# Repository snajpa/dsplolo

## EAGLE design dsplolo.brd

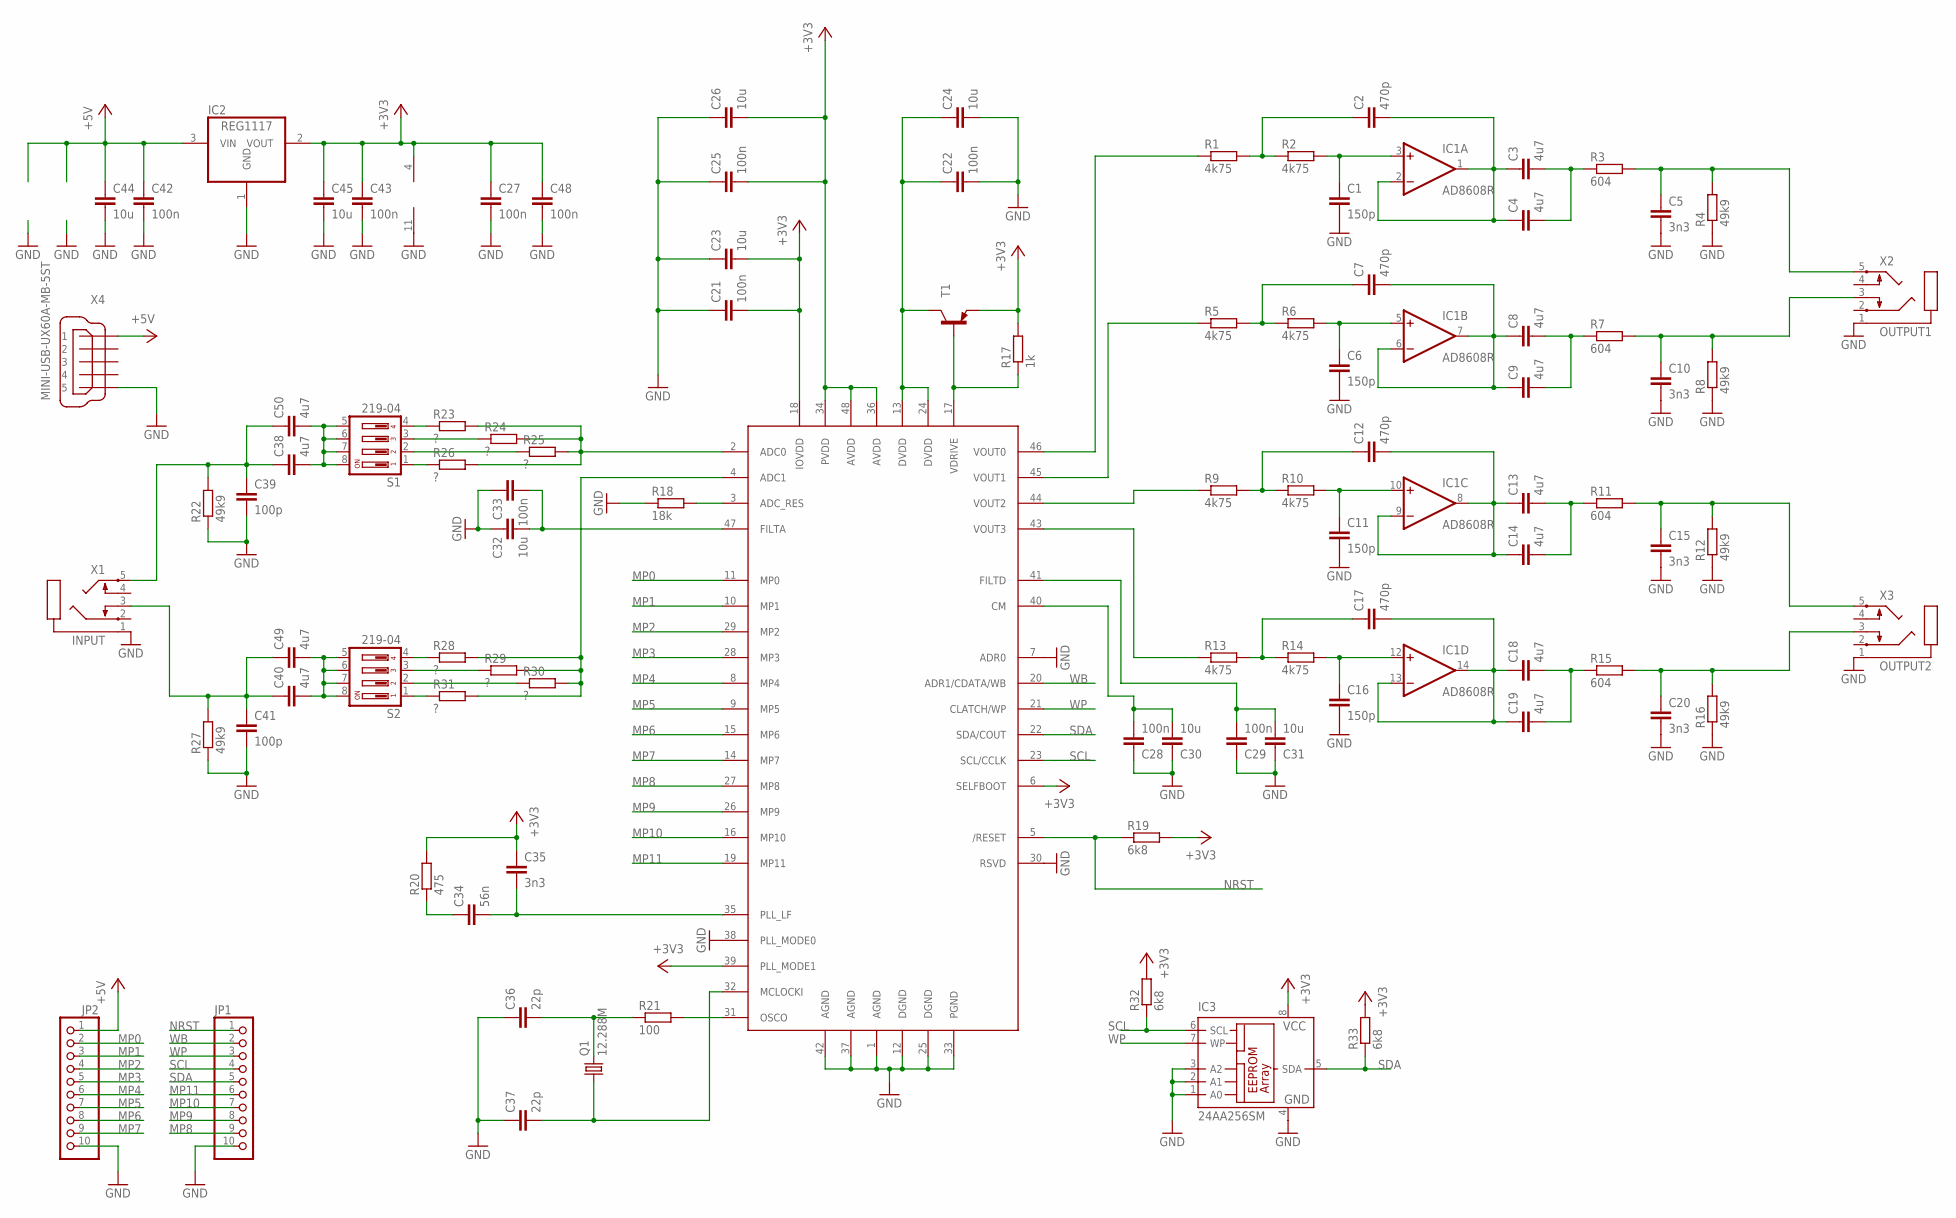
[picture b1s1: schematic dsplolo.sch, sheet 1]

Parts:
C1, C6, C11, C16: 150p; C1206
C2, C7, C12, C17: 470p; C1206
C3, C4, C8, C9, C13, C14, C18, C19, C38, C40, C49, C50: 4u7; C1206
C5, C10, C15, C20, C35: 3n3; C1206
C21, C22, C25, C27, C28, C29, C33, C42, C43, C48: 100n; C1206
C23, C24, C26, C30, C31, C32, C44, C45: 10u; C1206
C34: 56n; C1206
C36, C37: 22p; C1206
C39, C41: 100p; C1206
IC1: AD8608R; SO-14
IC2: REG1117; SOT223
IC3: 24AA256SM; SO-08M
JP1, JP2: PINHD-1X10; 1X10
Q1: 12.288M; HC49UP
R1, R2, R5, R6, R9, R10, R13, R14: 4k75; R1206
R3, R7, R11, R15: 604; R1206
R4, R8, R12, R16, R22, R27: 49k9; R1206
R17: 1k; R1206
R18: 18k; R1206
R19, R32, R33: 6k8; R1206
R20: 475; R1206
R21: 100; R1206
R23, R24, R25, R26, R28, R29, R30, R31: ?; R1206
S1, S2: 219-04; CTS-219-04
T1: BC857C-PNP-SOT23-BEC; SOT23-BEC
U$1: ADAU1701; LQFP-48
X1: INPUT; STX3100
X2: OUTPUT1; STX3100
X3: OUTPUT2; STX3100
X4: MINI-USB-UX60A-MB-5ST; UX60A-MB-5ST

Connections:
+3V3: C21.2, C23.2, C25.2, C26.2, C27.1, C35.1, C43.1, C45.1, C48.1, IC1.4 (V+), IC2.2 (VOUT), IC3.8 (VCC), R17.2, R19.2, R20.2, R32.2, R33.2, T1.E, U$1.6 (SELFBOOT), U$1.18 (IOVDD), U$1.34 (PVDD), U$1.36 (AVDD), U$1.39 (PLL_MODE1), U$1.48 (AVDD)
+5V: C42.1, C44.1, IC2.3 (VIN), JP2.1, X4.1
GND: C1.2, C5.2, C6.2, C10.2, C11.2, C15.2, C16.2, C20.2, C21.1, C22.2, C23.1, C24.2, C25.1, C26.1, C27.2, C28.1, C29.1, C30.1, C31.1, C32.1, C33.1, C36.1, C37.1, C39.2, C41.2, C42.2, C43.2, C44.2, C45.2, C48.2, IC1.11 (V-), IC2.1 (GND), IC3.1 (A0), IC3.2 (A1), IC3.3 (A2), IC3.4 (GND), JP1.10, JP2.10, R4.1, R8.1, R12.1, R16.1, R18.1, R22.1, R27.1, U$1.1 (AGND), U$1.7 (ADR0), U$1.12 (DGND), U$1.25 (DGND), U$1.30 (RSVD), U$1.33 (PGND), U$1.37 (AGND), U$1.38 (PLL_MODE0), U$1.42 (AGND), X1.1, X2.1, X3.1, X4.5
MP0: JP2.2, U$1.11 (MP0)
MP1: JP2.3, U$1.10 (MP1)
MP2: JP2.4, U$1.29 (MP2)
MP3: JP2.5, U$1.28 (MP3)
MP4: JP2.6, U$1.8 (MP4)
MP5: JP2.7, U$1.9 (MP5)
MP6: JP2.8, U$1.15 (MP6)
MP7: JP2.9, U$1.14 (MP7)
MP8: JP1.9, U$1.27 (MP8)
MP9: JP1.8, U$1.26 (MP9)
MP10: JP1.7, U$1.16 (MP10)
MP11: JP1.6, U$1.19 (MP11)
unnamed: C8.2, C9.2, R7.1
unnamed: C3.2, C4.2, R3.1
unnamed: C5.1, R3.2, R4.2, X2.5
unnamed: C2.1, R1.2, R2.1
unnamed: C1.1, IC1.3 (+IN), R2.2
unnamed: C2.2, C3.1, C4.1, IC1.1 (OUT), IC1.2 (-IN)
unnamed: C10.1, R7.2, R8.2, X2.3
unnamed: C7.1, R5.2, R6.1
unnamed: C6.1, IC1.5 (+IN), R6.2
unnamed: C7.2, C8.1, C9.1, IC1.6 (-IN), IC1.7 (OUT)
unnamed: C13.2, C14.2, R11.1
unnamed: C15.1, R11.2, R12.2, X3.5
unnamed: C12.1, R9.2, R10.1
unnamed: C11.1, IC1.10 (+IN), R10.2
unnamed: C12.2, C13.1, C14.1, IC1.8 (OUT), IC1.9 (-IN)
unnamed: C18.2, C19.2, R15.1
unnamed: C20.1, R15.2, R16.2, X3.3
unnamed: C17.1, R13.2, R14.1
unnamed: C16.1, IC1.12 (+IN), R14.2
unnamed: C17.2, C18.1, C19.1, IC1.13 (-IN), IC1.14 (OUT)
unnamed: R18.2, U$1.3 (ADC_RES)
unnamed: C22.1, C24.1, T1.C, U$1.13 (DVDD), U$1.24 (DVDD)
unnamed: R17.1, T1.B, U$1.17 (VDRIVE)
unnamed: R1.1, U$1.46 (VOUT0)
unnamed: R5.1, U$1.45 (VOUT1)
unnamed: R9.1, U$1.44 (VOUT2)
unnamed: R13.1, U$1.43 (VOUT3)
unnamed: C32.2, C33.2, U$1.47 (FILTA)
unnamed: C37.2, Q1.1, U$1.32 (MCLOCKI)
unnamed: C29.2, C31.2, U$1.41 (FILTD)
unnamed: C28.2, C30.2, U$1.40 (CM)
unnamed: C34.2, C35.2, U$1.35 (PLL_LF)
unnamed: C34.1, R20.1
unnamed: C36.2, Q1.2, R21.1
unnamed: R21.2, U$1.31 (OSCO)
unnamed: R23.1, S1.4
unnamed: C38.1, C39.1, C50.1, R22.2, X1.5
unnamed: C38.2, C50.2, S1.5, S1.6, S1.7, S1.8
unnamed: R24.1, S1.3
unnamed: R25.1, S1.2
unnamed: R26.1, S1.1
unnamed: R23.2, R24.2, R25.2, R26.2, U$1.2 (ADC0)
unnamed: C40.1, C41.1, C49.1, R27.2, X1.3
unnamed: C40.2, C49.2, S2.5, S2.6, S2.7, S2.8
unnamed: R28.1, S2.4
unnamed: R29.1, S2.3
unnamed: R30.1, S2.2
unnamed: R31.1, S2.1
unnamed: R28.2, R29.2, R30.2, R31.2, U$1.4 (ADC1)
NRST: JP1.1, R19.1, U$1.5 (/RESET)
SCL: IC3.6 (SCL), JP1.4, R32.1, U$1.23 (SCL/CCLK)
SDA: IC3.5 (SDA), JP1.5, R33.1, U$1.22 (SDA/COUT)
WB: JP1.2, U$1.20 (ADR1/CDATA/WB)
WP: IC3.7 (WP), JP1.3, U$1.21 (CLATCH/WP)

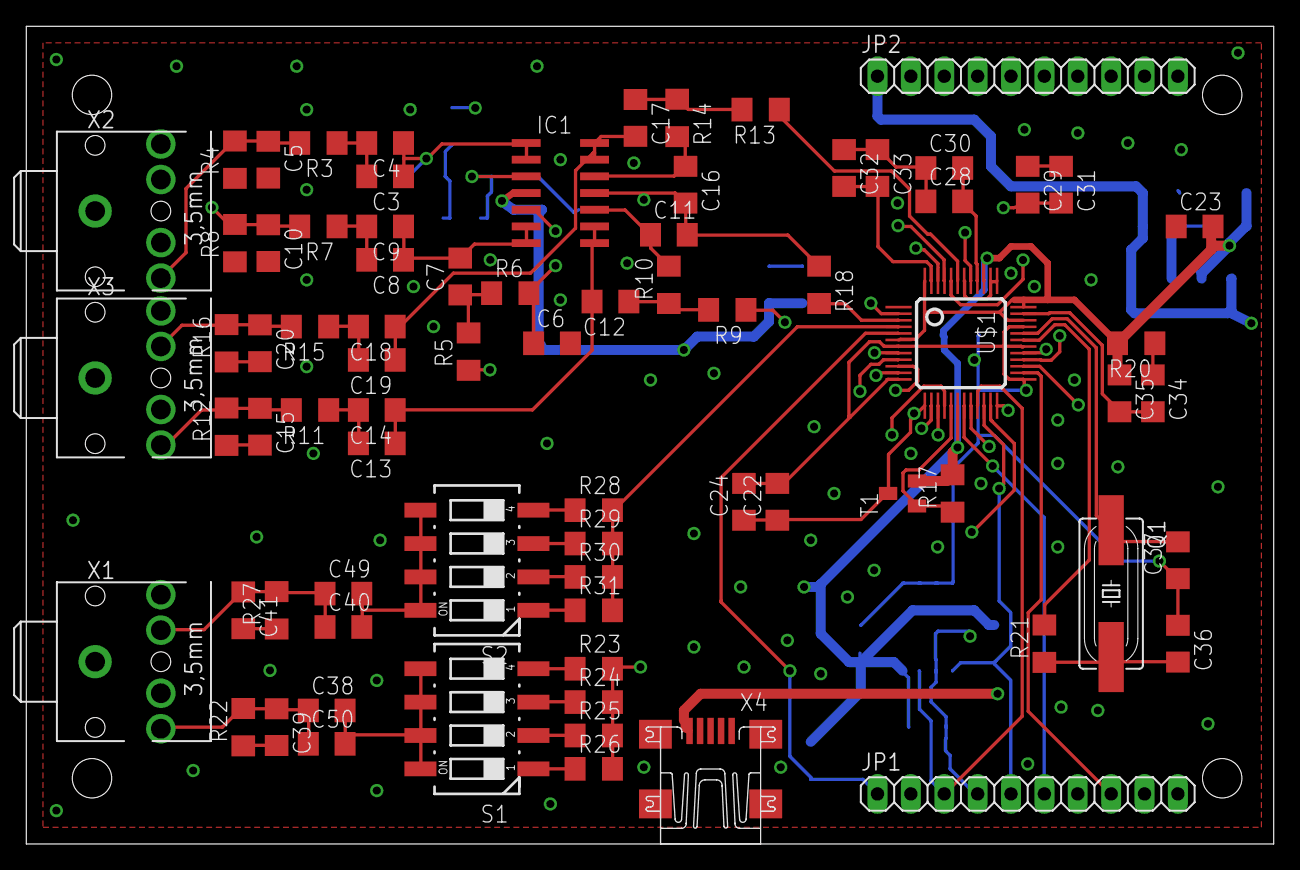
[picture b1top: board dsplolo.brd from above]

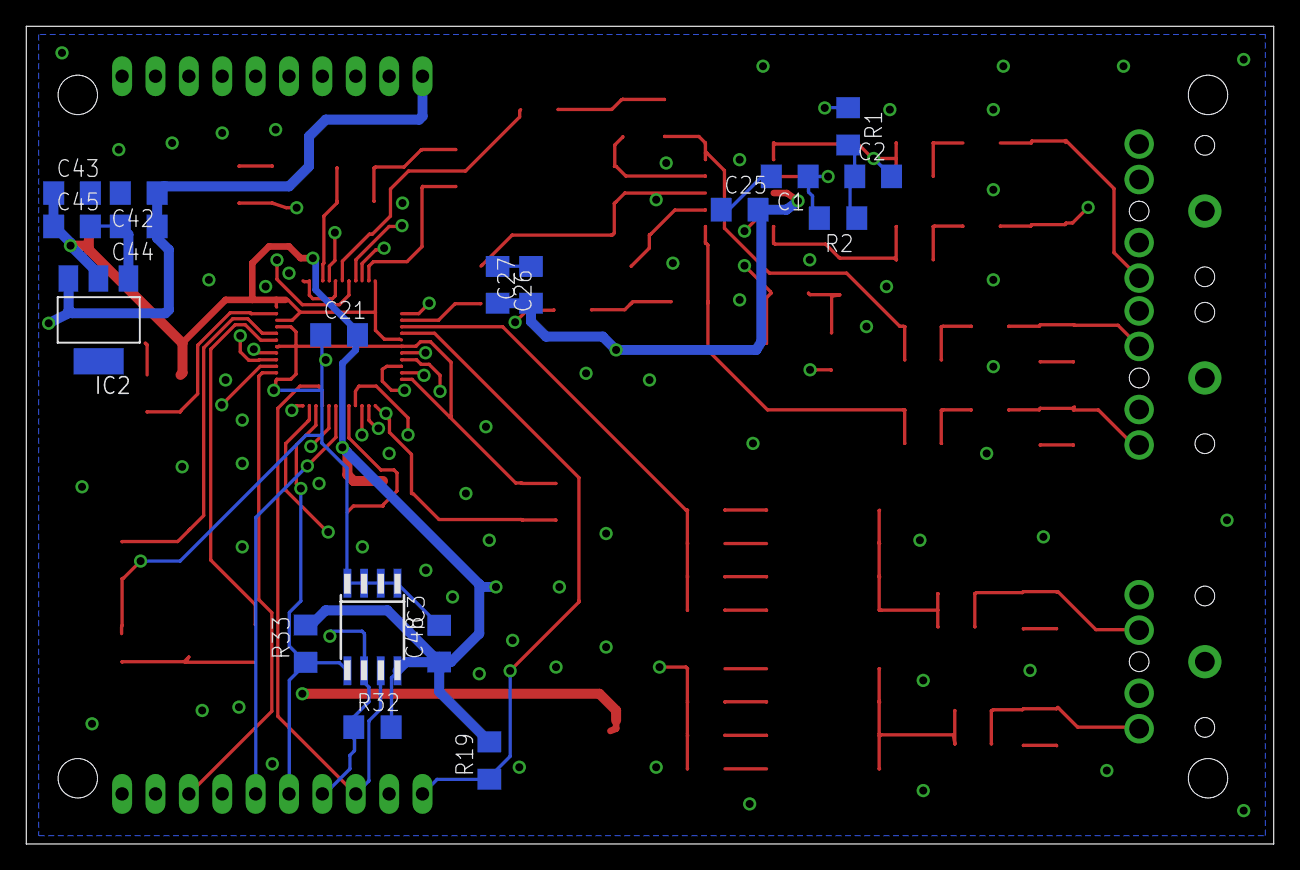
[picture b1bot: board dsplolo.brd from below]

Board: 4 copper layers, 94.9 x 62.2 mm, 95 parts (18 on the bottom side), 69 nets.

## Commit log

2016-11-30 freedsp schema for inspiration
2017-08-17 latest
2017-08-17 exports
